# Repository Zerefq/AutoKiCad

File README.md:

# AutoKiCad: от монтажа к принципиальной схеме

Обычно в EasyEDA и KiCad сначала рисуют схему, а потом плату. Здесь всё как в Tinkercad Circuits:

1. **Монтаж на макетной плате.** Вы ставите компоненты в «реальном» виде (резистор с цветными полосками, светодиод, NE555, Arduino Nano…) прямо в отверстия макетной платы. Ножки в одной полоске соединяются сами, как у настоящей платы. Где нужно, ставите перемычки от отверстия к отверстию.
2. **Схема строится сама**, и её видно справа прямо во время сборки. Программа строит список соединений, расставляет условные обозначения, прокладывает провода, ставит символы GND/+9V и метки цепей.
3. **Печатная плата** — на вкладке «Плата»: детали с настоящими посадочными местами, контур (прямоугольник, круг, сердце), линии связей.
4. **Экспорт** в EasyEDA или KiCad (схема и плата), где можно развести дорожки и заказать плату.

## Запуск

**В EasyEDA (основной способ).** Папка `easyeda-extension/` — это расширение для EasyEDA Standard. Установка описана в [easyeda-extension/README.md](easyeda-extension/README.md). Макетка открывается прямо в EasyEDA, компоненты берутся из библиотеки EasyEDA/LCSC (поиск по названию или номеру LCSC). Кнопка «Создать схему в EasyEDA» строит схему в редакторе, «Создать плату в EasyEDA» — плату.

**Отдельно.** Можно открыть `index.html` в браузере (Chrome, Edge, Firefox), без сервера и установки. Или через локальный сервер: `node tools/serve.js` и открыть адрес, который он напишет (обычно http://127.0.0.1:8765; если порт занят, сервер берёт следующий). Здесь доступны встроенные компоненты и экспорт в файлы. Поиск по библиотеке EasyEDA работает только внутри EasyEDA: сервер EasyEDA не принимает запросы с других страниц.
Программа открывается с пустой макетной платой. Готовые схемы лежат в меню **«Примеры»**:

| Пример | Что показывает |
|---|---|
| Светодиод с резистором | самая простая цепь: батарея, резистор, светодиод |
| Мигалка на NE555 | таймер в режиме генератора |
| Транзисторный ключ | кнопка включает светодиод через NPN-транзистор |
| Сумеречный выключатель | фоторезистор и транзистор: в темноте светодиод горит |
| Стабилизатор 5 В | 7805 делает +5 В из 9 В батареи |
| Arduino Nano: Blink | светодиод на выводе D13 |

Пример заменяет текущий проект, вернуть прежний можно через `Ctrl+Z`. Эти же примеры лежат файлами в папке `examples/` (*Открыть → .akc.json*). «Новый» даёт пустую макетную плату.

## Макетная плата

Плата на 30 столбцов, такая же, как настоящая half-size (есть и большая — на 60 столбцов):
- в каждом столбце отверстия **a–e** соединены между собой, отверстия **f–j** тоже, а канавка посередине их разделяет;
- шины **+** и **−** сверху и снизу соединены по всей длине. Верхние и нижние шины между собой не соединены, для этого ставят перемычки.

Компонент, поставленный на плату, «защёлкивается» ножками в отверстия. Занятые отверстия подсвечиваются зелёным. При наведении на отверстие подсвечивается вся цепь. Плату можно перетаскивать, и компоненты едут вместе с ней. Ножки разных компонентов, поставленные в одну точку, тоже соединяются, так что плата не обязательна.

## Управление

| Действие | Как |
|---|---|
| Добавить компонент | перетащить из левой панели или кликнуть по нему, затем по полю (Shift+клик — поставить несколько). Поле «Фильтр» над палитрой ищет по названию, номиналу и корпусу |
| Выделение | клик по компоненту; рамка левой кнопкой по пустому месту (выделяются компоненты, целиком попавшие в рамку); `Ctrl`/`Shift`+клик — добавить или убрать; `Ctrl+A` — всё. С `Shift`/`Ctrl` рамку можно начинать и поверх платы |
| Группа | перетаскивание любого выделенного компонента двигает всю группу; `R` поворачивает группу, выводы остаются в отверстиях; стрелки — сдвиг на 0.1" (`Shift` — на 0.5") |
| Копирование | `Ctrl+C` / `Ctrl+V` / `Ctrl+X`, `Ctrl+D` — копия рядом. Копия ставится справа от оригинала; вместе с платой копируются вставленные в неё детали и перемычки |
| Перемычка / провод | зажать мышь на отверстии или выводе и отпустить на другом. Или кликнуть дважды, при этом клики по пустому месту ставят точки изгиба. Провод к шине «−» становится чёрным, к «+» — красным |
| Режим | «Монтаж», «Монтаж + схема» (рядом, по умолчанию на широком экране), «Схема», «Плата», «3D» |
| Точка изгиба у готового провода | двойной клик по проводу; точки можно перетаскивать |
| Поворот / удаление / копия | `R` / `Del` / `Ctrl+D` |
| Отмена / повтор | `Ctrl+Z` / `Ctrl+Y` |
| Масштаб / сдвиг поля | колесо мыши / перетаскивание правой или средней кнопкой (как в EasyEDA), либо `Alt` + левой |
| Цвет нового провода | клавиши `1`…`8` или в свойствах провода |
| Имя цепи | выделить провод → «Имя цепи» (GND, VCC, +5V… превращаются в шины питания) |

На вкладке «Схема» символы можно перетаскивать, провода перестраиваются автоматически. «Авторасстановка» сбрасывает положение символов.

## Печатная плата

Вкладка **«Плата»**. Все детали проекта сразу стоят на плате со своими посадочными местами (площадки, отверстия, шелкография), а голубой пунктир показывает связи, которые нужно развести дорожками.

| Действие | Как |
|---|---|
| Переставить деталь | перетащить мышью (шаг 0.5 мм, с `Alt` — 0.1 мм) или стрелками (0.5 мм, с `Shift` — 2.54 мм); точные X, Y и угол — в панели справа |
| Повернуть | `R` — на 90°, `Shift+R` — на 45° |
| Посадочное место | в панели справа: например, резистор с шагом 10.16 / 7.62 мм, стоячий или SMD 0805 / 0603 |
| Форма платы | в панели справа, когда ничего не выделено: по деталям, прямоугольник, круг, сердце; размер и сдвиг контура; цвет маски (только для вида) |
| Корпуса деталей | в панели справа: «Показывать» (по умолчанию — детали видны сверху, как на вкладке «3D»), «Полупрозрачные» (видны площадки под корпусом), «Скрыть» |

Посадочные места встроенных деталей взяты из библиотеки KiCad, у деталей из библиотеки EasyEDA/LCSC — их родные. Дорожки программа не прокладывает: это делается в EasyEDA (*Трассировка → Автотрассировка* или вручную) или в KiCad.

## 3D

Вкладка **«3D»** показывает плату в объёме: маска выбранного цвета, площадки, шелкография и детали — резисторы с цветными полосками по номиналу, микросхемы, светодиоды, кнопки, разъёмы. Тяните мышью — вращение, колесо — масштаб, правая кнопка — сдвиг; кнопки «Наклон», «Сверху», «Спереди», «Сбоку» в панели справа.

К каждому посадочному месту привязана 3D-модель из библиотеки EasyEDA, поэтому в EasyEDA (*Вид → 3D-вид*) плата видна с настоящими моделями деталей, а в 2D-редакторе платы включён слой **3DModel** — контуры корпусов деталей. В расширении кнопка **«3D-вид в EasyEDA»** создаёт плату и сразу открывает её 3D-вид с тем же цветом маски.

Проект автоматически сохраняется в браузере. «Сохранить» скачивает файл `.akc.json`.

## Экспорт

- **KiCad, готовый проект (`.zip`)**: `.kicad_pro`, схема, плата, библиотека символов `AutoKiCad.kicad_sym` и `sym-lib-table`. Распакуйте архив и откройте `.kicad_pro`. Проверено в KiCad 10.0.6: демо‑схема проходит ERC без ошибок и предупреждений.
- **KiCad, только схема (`.kicad_sch`)**: один файл, символы встроены в него, у компонентов прописаны посадочные места (footprint). EasyEDA Pro импортирует KiCad‑проекты: *Файл → Импорт → KiCad*.
- **EasyEDA Standard (`.json`)**: исходник схемы. В EasyEDA: *Документ → Открыть → EasyEDA Source…* или просто перетащите файл в окно. Набор полей сверен с парсером EasyEDA 6.5.51.
- **EasyEDA Standard — плата (`.json`)**: контур, посадочные места, цепи на площадках, видимые связи. Открывается так же. Проверено в EasyEDA 6.5.60: все детали и цепи на месте.
- **KiCad — плата (`.kicad_pcb`)**: то же для KiCad; входит и в готовый проект (`.zip`). Проверено `kicad-cli pcb drc`: без замыканий и нарушений зазоров. Предупреждение «посадочное место не совпадает с библиотекой» снимается командой *Инструменты → Обновить посадочные места из библиотеки*.
- **Netlist (`.net`)**: список соединений в формате KiCad, для загрузки в редактор плат.
- **BOM (`.csv`)**: перечень элементов, как в EasyEDA. Одинаковые детали идут одной строкой (обозначения, номинал, корпус, посадочное место, количество, номер LCSC). Открывается в Excel.
- **PNG / SVG**: картинка схемы.
- **Печать / PDF**: схема на листе A4; в окне печати можно выбрать «Сохранить как PDF».

## Компоненты

Встроенные: макетные платы на 30 и 60 столбцов, резистор, конденсатор, электролитический конденсатор, катушка индуктивности, кварцевый резонатор, светодиод, диод, стабилитрон, NPN и PNP транзисторы, N-MOSFET, кнопка, переключатель, потенциометр, фоторезистор, пищалка, мотор, батарея, стабилизатор 78xx (выход сам становится цепью +5V/+12V… по номиналу), таймер NE555, операционный усилитель LM358, микроконтроллер ATtiny85, адресный RGB-светодиод WS2812B, разъём USB-C, контакт-отверстие, Arduino Nano, разъёмы 1×2…1×8, символы питания и земли. В EasyEDA к ним добавляется вся библиотека EasyEDA/LCSC через поиск.

Готовые файлы примеров лежат в папке `examples/`: все примеры как проекты (`.akc.json`), мигалка — ещё и в форматах KiCad и EasyEDA.

## Как это устроено

```
js/components.js     библиотека: внешний вид (монтаж) + символ (схема) + footprint
js/footprints.js     посадочные места из библиотеки KiCad (собирается tools/build-footprints.js)
js/ee-footprints.js  такие же посадочные места из библиотеки EasyEDA и их 3D-модели (собирается tools/build-ee-footprints.js)
js/examples.js       примеры из меню «Примеры» (компоненты ставятся в отверстия по имени: f14, TP1…)
js/editor.js         редактор монтажа
js/easyeda-lib.js    библиотека EasyEDA: поиск, загрузка, символ + вид на макетке по посадочному месту
js/netlist.js        провода + полоски макетки + совпадающие ножки → цепи (union-find), имена, проверки
js/schematic.js      автогенерация схемы: расстановка + трассировка
js/schview.js        отрисовка и просмотр схемы
js/export-kicad.js   .kicad_sch и .net
js/export-easyeda.js EasyEDA Standard JSON
js/pcb.js            печатная плата: расстановка, контур, площадки с цепями, связи, экспорт в EasyEDA и KiCad
js/pcbview.js        вкладка «Плата»
js/pcb3d.js          вкладка «3D»
js/app.js            интерфейс, история, файлы, пример
easyeda-extension/   расширение EasyEDA: main.js (окно, сборка схемы и платы через API EasyEDA), ui.txt (собранный интерфейс)
tools/build-extension.js  сборка ui.txt из исходников
tools/build-footprints.js сборка js/footprints.js из библиотеки KiCad
tools/build-ee-footprints.js сборка js/ee-footprints.js: подбор посадочных мест EasyEDA по расположению площадок
tools/serve.js       локальный сервер
```

Компоненты из библиотеки EasyEDA — **JLCEDA/EasyEDA Official Library**, https://lceda.cn/ · https://easyeda.com.

Посадочные места встроенных деталей (`js/footprints.js`) — из **KiCad footprint library** (https://gitlab.com/kicad/libraries/kicad-footprints), лицензия CC-BY-SA 4.0 с исключением: платы, сделанные с этими посадочными местами, можно распространять и использовать без ограничений.

**Генерация схемы:**
1. Цепи питания (GND, +5V, VCC… или источник «Питание») рисуются символами питания, а не проводами.
2. Символы расставляются жадным алгоритмом: первым ставится самый связанный компонент, остальные ставятся рядом с теми, с кем у них больше всего общих цепей.
3. Каждая сигнальная цепь соединяется по минимальному остовному дереву Г‑ и Z‑образными проводами. Провода не проходят через корпуса и не касаются чужих цепей, при этом пересечения разрешены. Если путь не найден, вместо провода ставятся метки с именем цепи.
4. Неподключённые выводы помечаются крестиком (no‑connect).

## Добавить свой компонент

В `js/components.js` добавьте объект в `defs`:
- `visual` — как компонент выглядит в монтаже: SVG‑функция `draw` и координаты выводов в пикселях (10px = 2.54 мм). Расстояния между выводами должны быть кратны 10px, чтобы ножки попадали в отверстия макетки. `hit` — область захвата мышью, обычно только корпус;
- `sym` — символ схемы в единицах U (1U = 2.54 мм). Выводы должны стоять на целых координатах, `dir` указывает от точки подключения к корпусу. Для микросхем есть готовый генератор `makeIC(left, right, width)`;
- `footprint` — посадочное место KiCad, `fpAlt` — альтернативы. После добавления выполните `node tools/build-footprints.js`, чтобы посадочное место попало в `js/footprints.js`, затем `node tools/build-ee-footprints.js` — для «Конвертировать в печатную плату» в EasyEDA. Если номера площадок не совпадают с номерами выводов (как у USB-C), задайте `padMap: { площадка: вывод }`.

## Лицензия

MIT, © 2026 Madamin — см. [LICENSE.md](LICENSE.md). На платах-примерах — надпись by_Madamin.

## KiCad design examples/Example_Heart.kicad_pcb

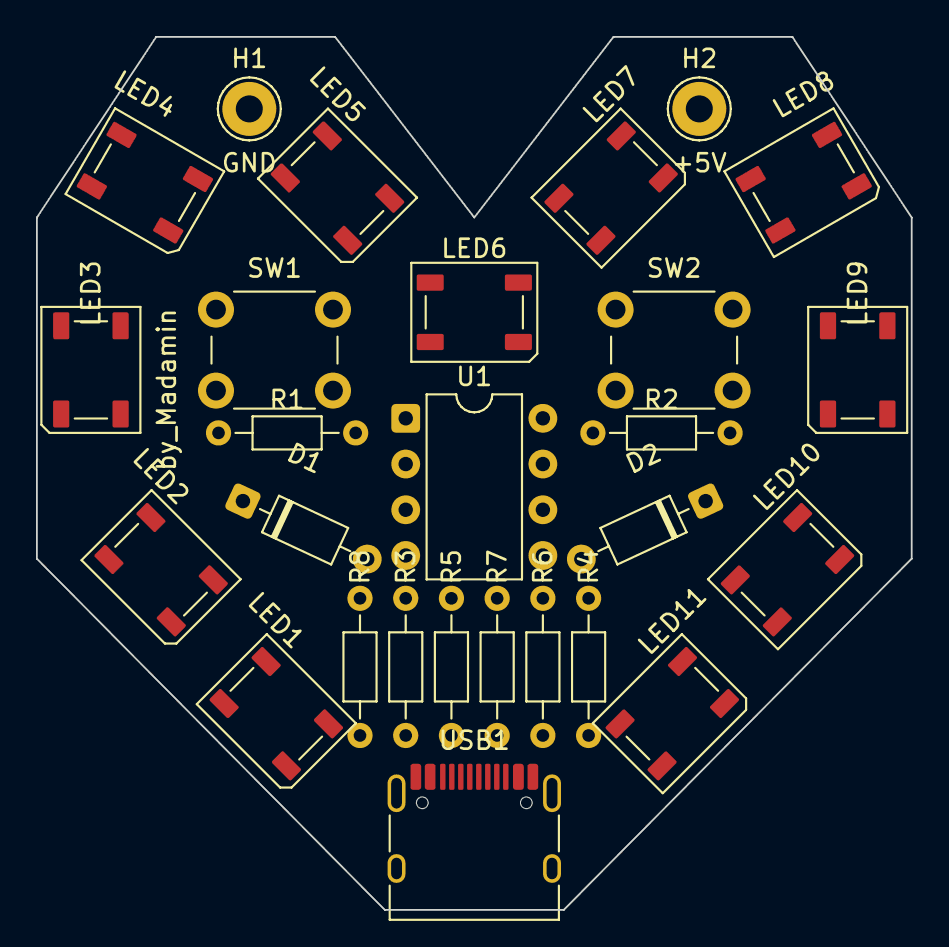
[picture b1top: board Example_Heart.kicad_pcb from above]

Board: 2 copper layers, 48.6 x 48.5 mm, 27 parts (0 on the bottom side), 24 nets, no tracks yet.

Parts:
D1, D2: BZX55C3V6; D_DO-35_SOD27_P7.62mm_Horizontal
H1: GND; TestPoint_THTPad_D3.0mm_Drill1.5mm
H2: +5V; TestPoint_THTPad_D3.0mm_Drill1.5mm
LED1, LED2, LED3, LED4, LED5, LED6, LED7, LED8, LED9, LED10, LED11: WS2812B; LED_WS2812B_PLCC4_5.0x5.0mm_P3.2mm
R1, R2: 1k; R_Axial_DIN0204_L3.6mm_D1.6mm_P7.62mm_Horizontal
R3, R4: 68; R_Axial_DIN0204_L3.6mm_D1.6mm_P7.62mm_Horizontal
R5: 1.5k; R_Axial_DIN0204_L3.6mm_D1.6mm_P7.62mm_Horizontal
R6: 330; R_Axial_DIN0204_L3.6mm_D1.6mm_P7.62mm_Horizontal
R7, R8: 5.1k; R_Axial_DIN0204_L3.6mm_D1.6mm_P7.62mm_Horizontal
SW1, SW2: BTN; SW_PUSH_6mm
U1: ATtiny85; DIP-8_W7.62mm
USB1: USB-C; USB_C_Receptacle_HRO_TYPE-C-31-M-12

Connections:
+5V: H2.1, LED1.1, LED2.1, LED3.1, LED4.1, LED5.1, LED6.1, LED7.1, LED8.1, LED9.1, LED10.1, LED11.1, R5.2, U1.8, USB1.A4, USB1.A9, USB1.B4, USB1.B9
GND: D1.2, D2.2, H1.1, LED1.3, LED2.3, LED3.3, LED4.3, LED5.3, LED6.3, LED7.3, LED8.3, LED9.3, LED10.3, LED11.3, R7.1, R8.1, SW1.2, SW2.1, U1.4, USB1.A1, USB1.A12, USB1.B1, USB1.B12, USB1.SH
N1: R7.2, USB1.A5
N2: R8.2, USB1.B5
N3: R4.1, R5.1, USB1.A7, USB1.B7
N4: R3.1, USB1.A6, USB1.B6
N5: D2.1, R4.2, U1.2
N6: D1.1, R3.2, U1.3
N7: R2.2, SW2.2
N8: R2.1, U1.7
N9: R1.1, U1.6
N10: R6.1, U1.5
N11: R1.2, SW1.1
N12: LED1.4, R6.2
N13: LED1.2, LED2.4
N14: LED2.2, LED3.4
N15: LED3.2, LED4.4
N16: LED4.2, LED5.4
N17: LED5.2, LED6.4
N18: LED6.2, LED7.4
N19: LED7.2, LED8.4
N20: LED8.2, LED9.4
N21: LED9.2, LED10.4
N22: LED10.2, LED11.4
